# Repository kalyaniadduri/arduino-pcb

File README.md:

# arduino-pcb
A basic arduino board is designed using pcb designing by eagle software.
The repository is having the following :
1.schematic file and its images
2.pcb board file and its images
3.gerber files

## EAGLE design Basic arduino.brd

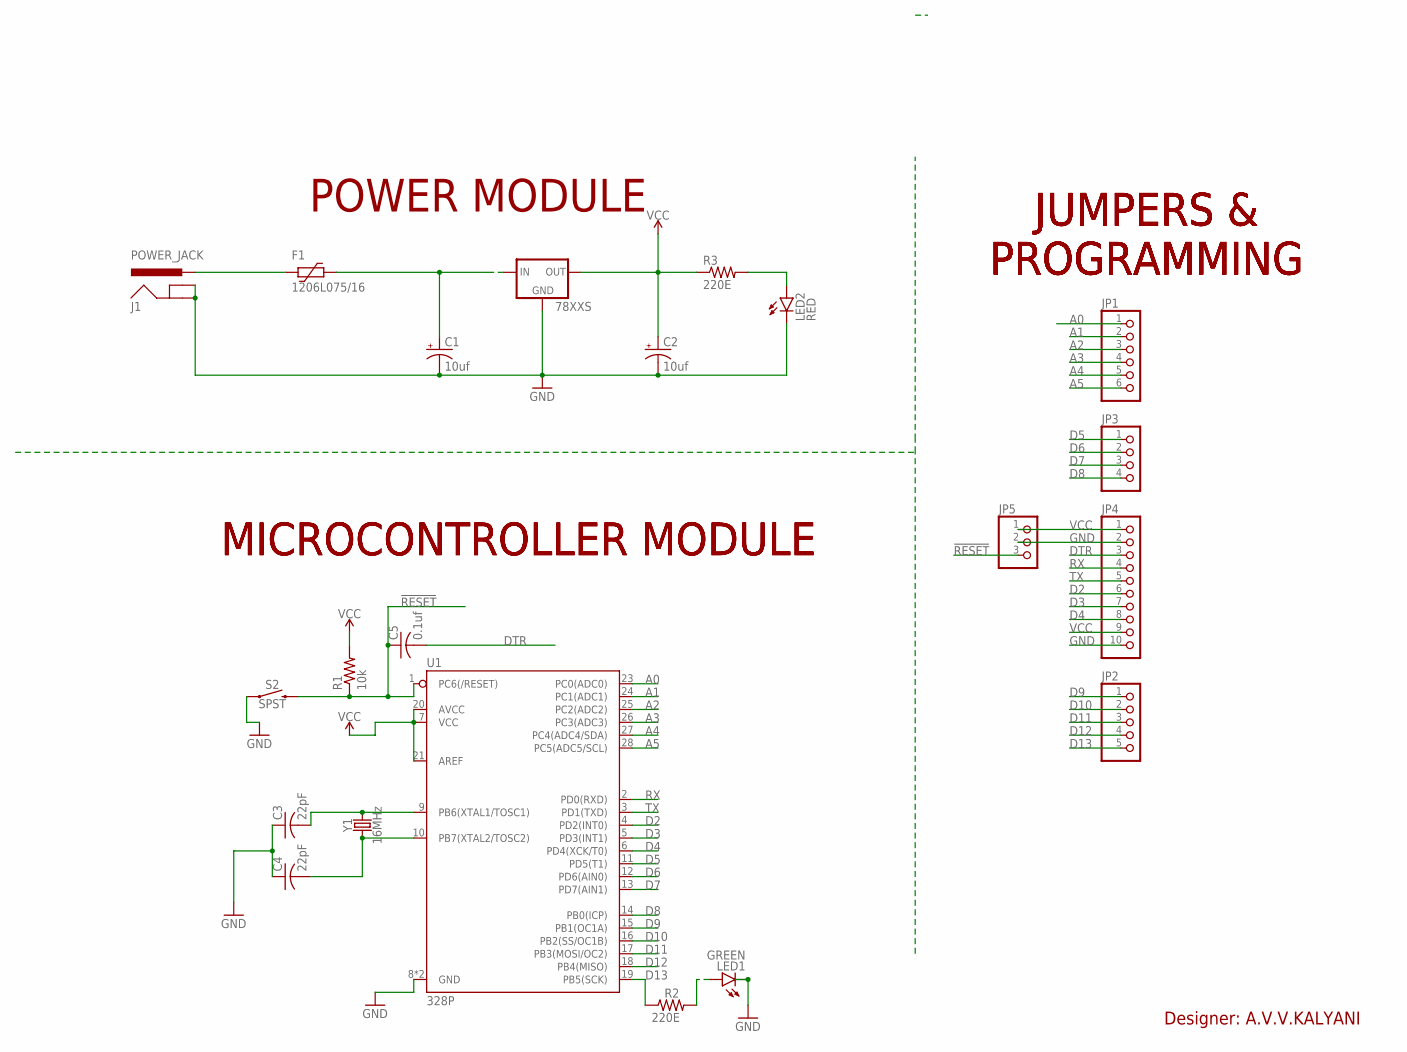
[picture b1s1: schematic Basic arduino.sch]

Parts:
78XXS: 78XXS
C1, C2: 10uf; E2,5-6
C3, C4: 22pF; C025-025X050
C5: 0.1uf; C025-024X044
F1: 1206L075/16; 1206L
J1: POWER_JACK; POWER_JACK_PTH
JP1: PINHD-1X6; 1X06
JP2: PINHD-1X5; 1X05
JP3: PINHD-1X4; 1X04
JP4: PINHD-1X10; 1X10
JP5: PINHD-1X3; 1X03
LED1: GREEN; LED3MM
LED2: RED; LED3MM
R1: 10k; 0204/7
R2, R3: 220E; 0204/7
S2: SPST; TACTILE_SWITCH_PTH_6.0MM
U1: 328P; DIP28
Y1: 16MHz; HC49US

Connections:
!RESET: C5.1, JP5.3, R1.1, S2.3 (2), U1.1 (PC6(/RESET))
A0: JP1.1, U1.23 (PC0(ADC0))
A1: JP1.2, U1.24 (PC1(ADC1))
A2: JP1.3, U1.25 (PC2(ADC2))
A3: JP1.4, U1.26 (PC3(ADC3))
A4: JP1.5, U1.27 (PC4(ADC4/SDA))
A5: JP1.6, U1.28 (PC5(ADC5/SCL))
D2: JP4.6, U1.4 (PD2(INT0))
D3: JP4.7, U1.5 (PD3(INT1))
D4: JP4.8, U1.6 (PD4(XCK/T0))
D5: JP3.1, U1.11 (PD5(T1))
D6: JP3.2, U1.12 (PD6(AIN0))
D7: JP3.3, U1.13 (PD7(AIN1))
D8: JP3.4, U1.14 (PB0(ICP))
D9: JP2.1, U1.15 (PB1(OC1A))
D10: JP2.2, U1.16 (PB2(SS/OC1B))
D11: JP2.3, U1.17 (PB3(MOSI/OC2))
D12: JP2.4, U1.18 (PB4(MISO))
D13: JP2.5, R2.1, U1.19 (PB5(SCK))
DTR: C5.2, JP4.3
GND: 78XXS.GND, C1.-, C2.-, C3.1, C4.1, J1.GND, J1.GNDBREAK, JP4.2, JP4.10, JP5.2, LED1.K (C), LED2.K (C), S2.1, U1.8 (GND), U1.22 (GND)
unnamed: 78XXS.IN, C1.+, F1.1
unnamed: C3.2, U1.9 (PB6(XTAL1/TOSC1)), Y1.2
unnamed: C4.2, U1.10 (PB7(XTAL2/TOSC2)), Y1.1
unnamed: LED2.A, R3.2
unnamed: F1.2, J1.PWR
unnamed: LED1.A, R2.2
RX: JP4.4, U1.2 (PD0(RXD))
TX: JP4.5, U1.3 (PD1(TXD))
VCC: 78XXS.OUT, C2.+, JP4.1, JP4.9, JP5.1, R1.2, R3.1, U1.7 (VCC), U1.20 (AVCC), U1.21 (AREF)

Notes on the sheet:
MICROCONTROLLER MODULE
POWER MODULE
JUMPERS & PROGRAMMING
Designer: A.V.V.KALYANI

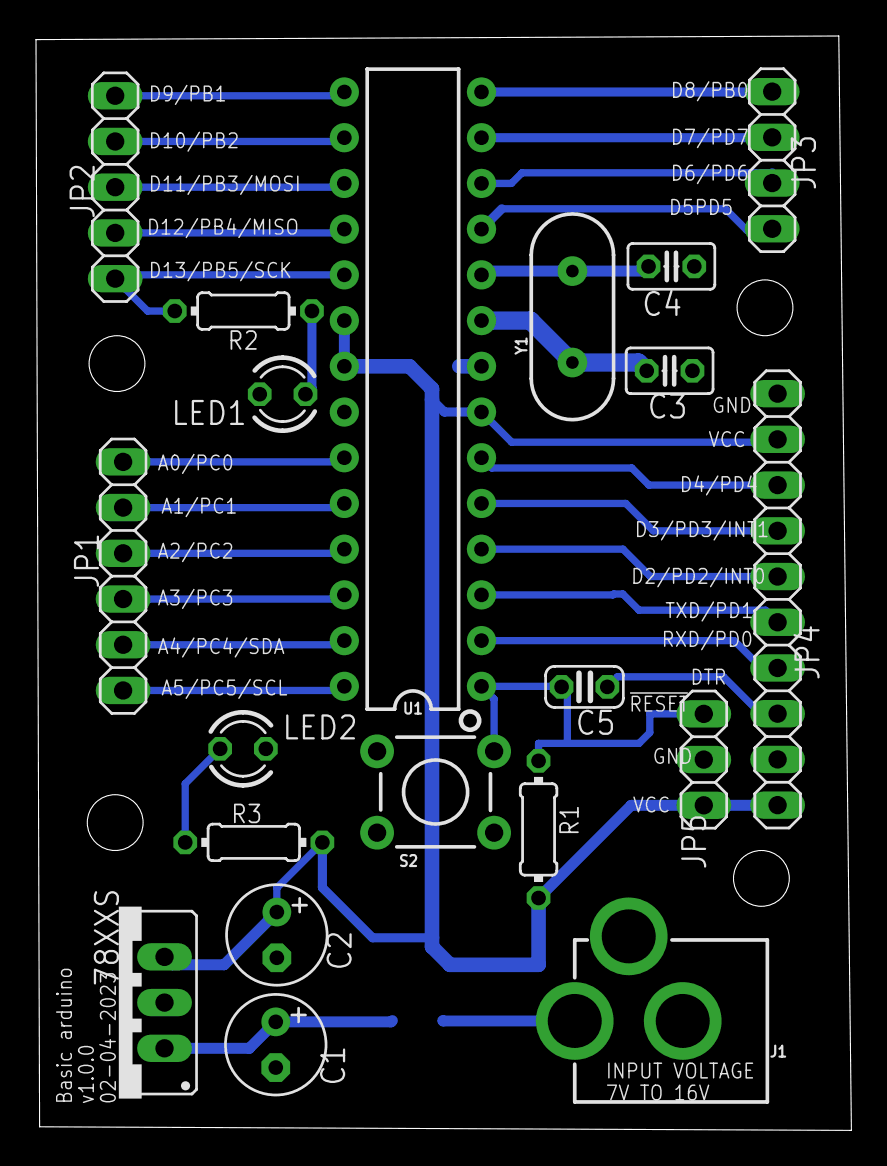
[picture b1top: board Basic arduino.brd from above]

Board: 2 copper layers, 45.3 x 60.8 mm, 21 parts (1 on the bottom side), 30 nets.

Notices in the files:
parts and their libraries:
SparkFun-Connectors: Licensing: Creative Commons ShareAlike 4.0 International - https://creativecommons.org/licenses/by-sa/4.0
